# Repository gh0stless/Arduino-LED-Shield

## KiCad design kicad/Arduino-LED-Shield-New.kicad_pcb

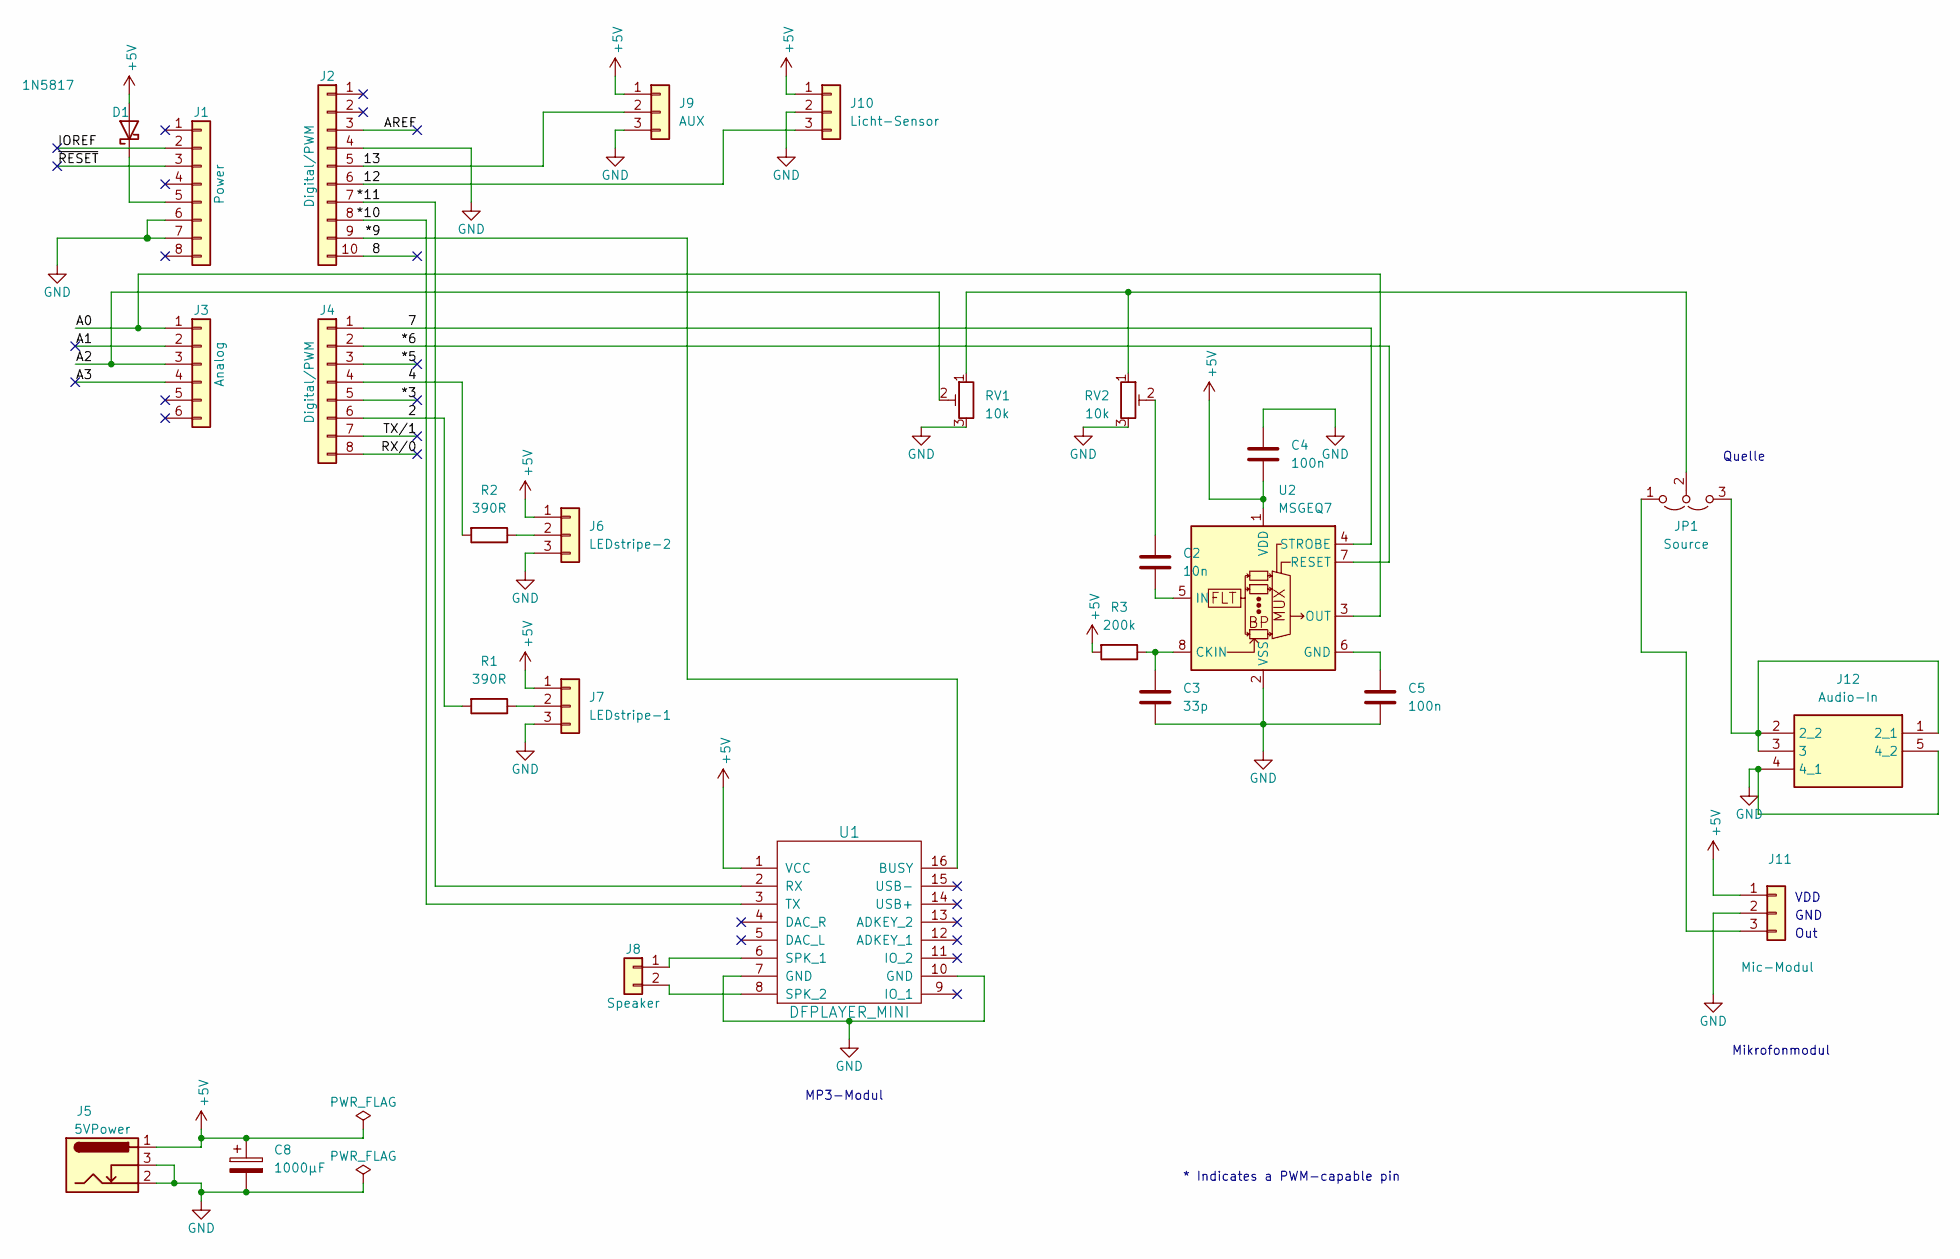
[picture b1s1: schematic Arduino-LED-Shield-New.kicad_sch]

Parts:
C2: 10n; C_Disc_D3.0mm_W2.0mm_P2.50mm
C3: 33p; C_Disc_D3.0mm_W2.0mm_P2.50mm
C4, C5: 100n; C_Disc_D3.0mm_W2.0mm_P2.50mm
C8: 1000µF; CP_Radial_D8.0mm_P5.00mm
D1: 1N5817; D_DO-41_SOD81_P10.16mm_Horizontal
J1: Power; PinSocket_1x08_P2.54mm_Vertical
J2: Digital/PWM; PinSocket_1x10_P2.54mm_Vertical
J3: Analog; PinSocket_1x06_P2.54mm_Vertical
J4: Digital/PWM; PinSocket_1x08_P2.54mm_Vertical
J5: 5VPower; DC-Buchse
J6: LEDstripe-2; PCB_Terminal_Block_3-P3.5
J7: LEDstripe-1; PCB_Terminal_Block_3-P3.5
J8: Speaker; PinHeader_1x02_P2.54mm_Horizontal
J9: AUX; PinSocket_1x03_P2.54mm_Horizontal
J10: Licht-Sensor; PinSocket_1x03_P2.54mm_Horizontal
J11: Mic-Modul; PinSocket_1x03_P2.54mm_Horizontal
J12: Audio-In; PJ313; Manufacturer_Part_Number PJ-313
JP1: Source; PinHeader_1x03_P2.54mm_Vertical
R1, R2: 390R; R_Axial_DIN0207_L6.3mm_D2.5mm_P10.16mm_Horizontal
R3: 200k; R_Axial_DIN0207_L6.3mm_D2.5mm_P10.16mm_Horizontal
RV1, RV2: 10k; Potentiometer_Runtron_RM-063_Horizontal
U1: DFPLAYER_MINI; DFR0299
U2: MSGEQ7; DIP-8_W7.62mm

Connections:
+5V: C4.2, D1.2 (A), J5.1, J6.1, J7.1, J9.1, J10.1, J11.1, R3.2, U1.1 (VCC), U2.1 (VDD); also elsewhere on the board
/2: J4.6, R1.2
/4: J4.4, R2.2
/7: J4.1, U2.4 (STROBE)
/8: J2.10
/12: J2.6, J10.3
/13: J2.5, J9.2
/*3: J4.5
/*5: J4.3
/*6: J4.2, U2.7 (RESET)
/*9: J2.9, U1.16 (BUSY)
/*10: J2.8, U1.3 (TX)
/*11: J2.7, U1.2 (RX)
/A0: J3.1, U2.3 (OUT)
/A1: J3.2
/A2: J3.3, RV1.2
/A3: J3.4
/AREF: J2.3
/IOREF: J1.2
/RX/0: J4.8
/TX/1: J4.7
/~RESET: J1.3
GND: C3.2, C4.1, C5.2, J1.6, J1.7, J2.4, J5.2, J5.3, J6.3, J7.3, J9.3, J10.2, J11.2, J12.4 (4_1), J12.5 (4_2), RV1.3, RV2.3, U1.7 (GND), U1.10 (GND), U2.2 (VSS); also elsewhere on the board
unnamed: C2.1, RV2.2
unnamed: D1.1 (K), J1.5
unnamed: J6.2, R2.1
unnamed: J7.2, R1.1
unnamed: J8.1, U1.6 (SPK_1)
unnamed: J8.2, U1.8 (SPK_2)
unnamed: J11.3, JP1.1 (A)
unnamed: J12.1 (2_1), J12.2 (2_2), J12.3, JP1.3 (B)
unnamed: JP1.2 (C), RV1.1, RV2.1
unnamed: C3.1, R3.1, U2.8 (CKIN)
unnamed: C5.1, U2.6 (GND)
unnamed: C2.2, U2.5 (IN)

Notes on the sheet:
GND
Mikrofonmodul
Out
VDD
MP3-Modul
* Indicates a PWM-capable pin
Quelle

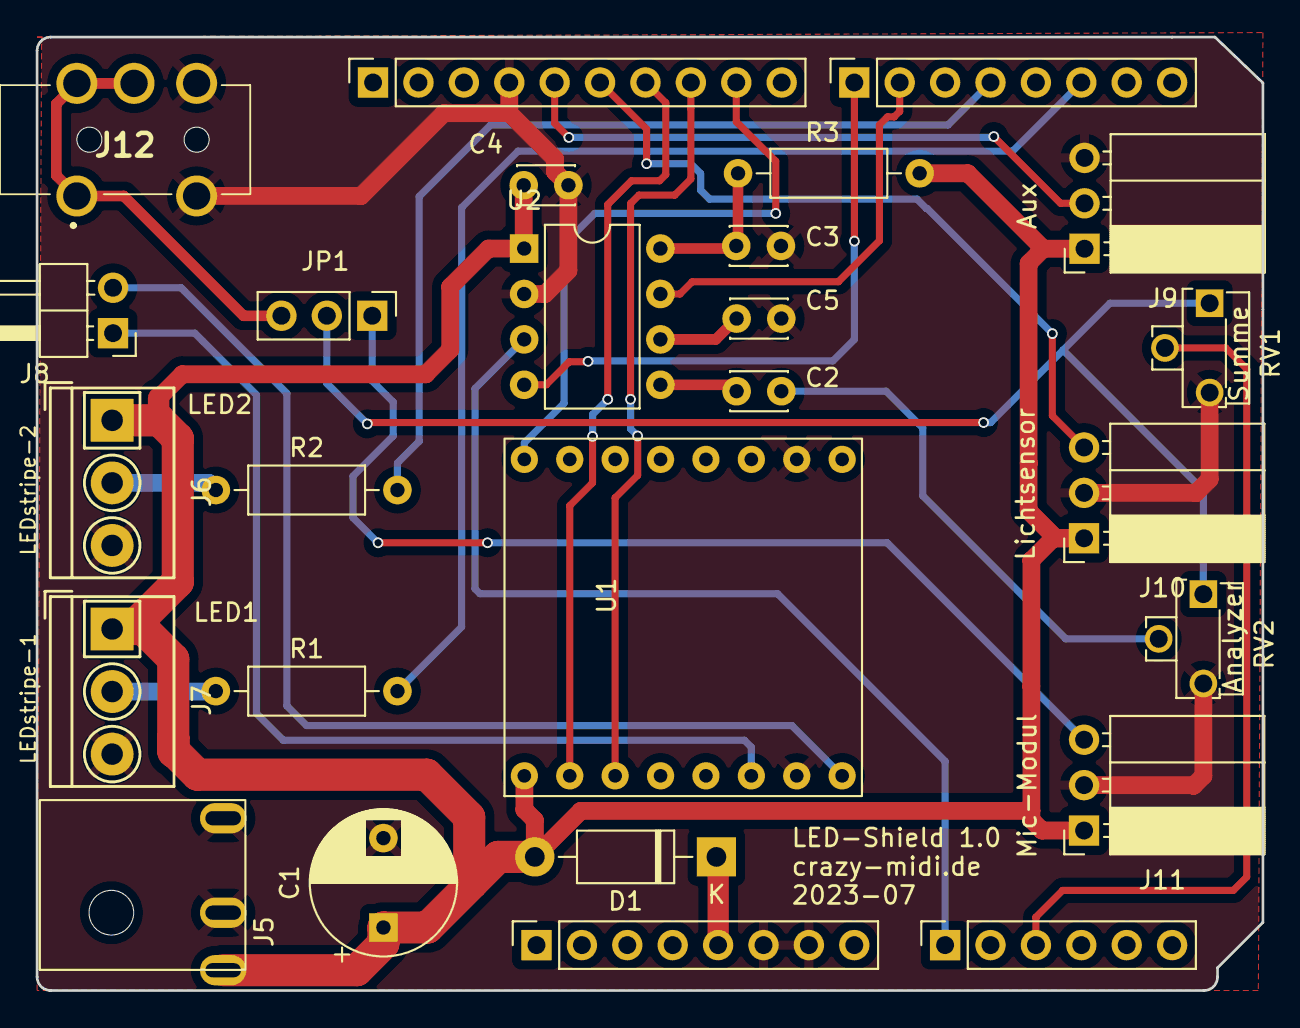
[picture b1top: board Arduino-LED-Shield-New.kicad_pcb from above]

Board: 2 copper layers, 68.6 x 53.3 mm, 26 parts (0 on the bottom side), 25 nets.

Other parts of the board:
C1: 1000µF; CP_Radial_D8.0mm_P5.00mm

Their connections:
+5V: C1.1; also elsewhere on the board
GND: C1.2; also elsewhere on the board

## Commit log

2023-10-04 init
